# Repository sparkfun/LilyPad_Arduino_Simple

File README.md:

LilyPad Arduino Simple
======================

[*LilyPad Arduino Simple Board (DEV-10274)*](https://www.sparkfun.com/products/10274)

This LilyPad board is smaller than the LilyPad Main Board, with fewer pins. However, it does have a 
built-in power supply socket, and an on/off switch. 

Repository Contents
-------------------

* **/Hardware** - All Eagle design files (.brd, .sch, .STL)
* **/Production** - Test bed files and production panel files

License Information
-------------------
The hardware is released under [Creative Commons ShareAlike 4.0 International](https://creativecommons.org/licenses/by-sa/4.0/).
The code is beerware; if you see me (or any other SparkFun employee) at the local, and you've found our code helpful, please buy us a round!

Distributed as-is; no warranty is given.

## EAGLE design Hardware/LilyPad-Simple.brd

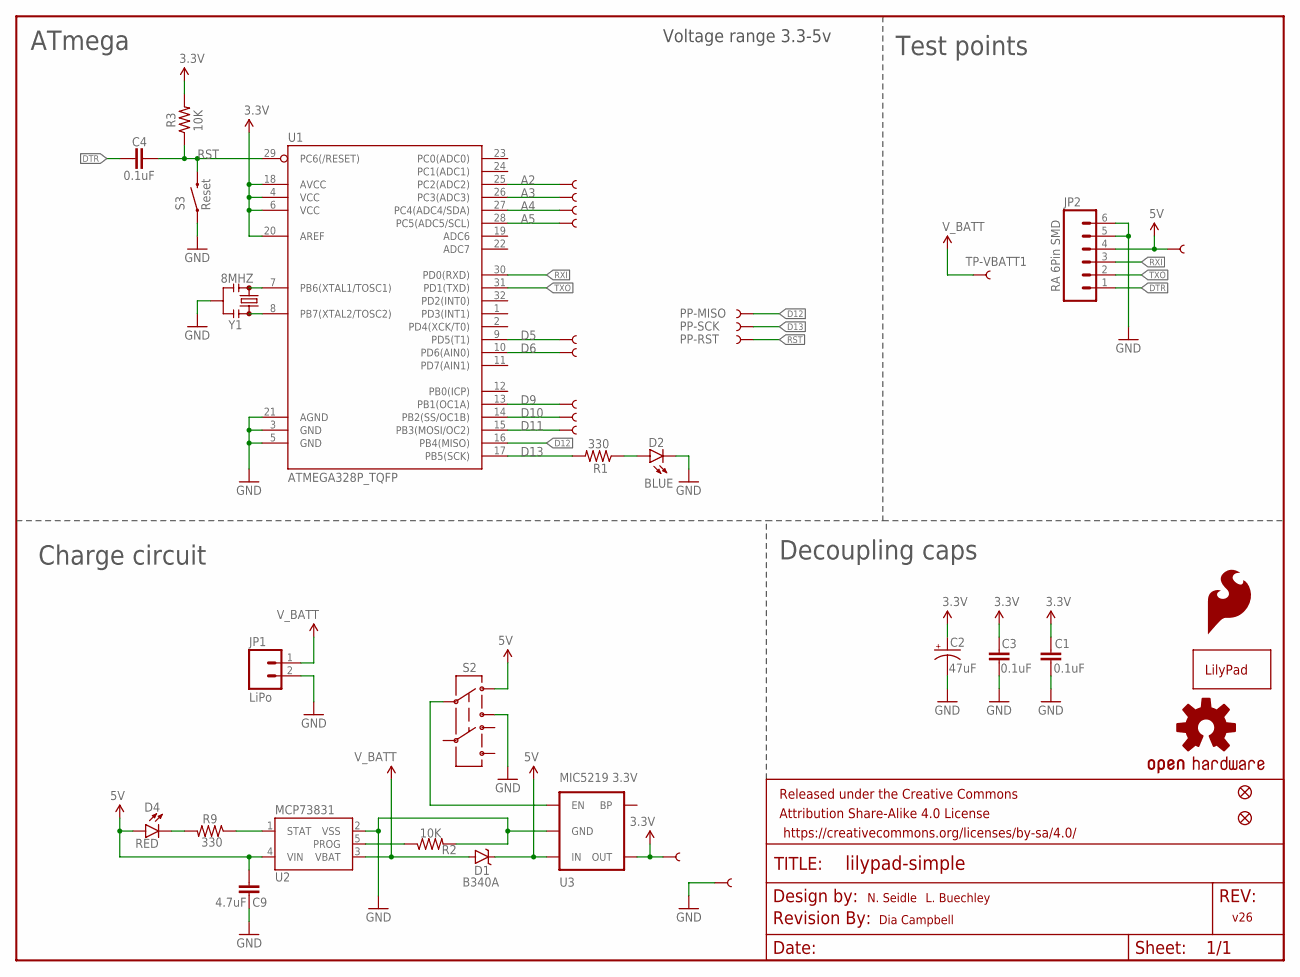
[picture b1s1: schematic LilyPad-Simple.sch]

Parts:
A2/16, A3/17, A4/18, A5/19: SEWTAP9; PETAL-LONG-1-2SIDE
C1, C3, C4: 0.1uF; 0603-CAP
C2: 47uF; EIA3528
C9: 4.7uF; 0603-CAP
D1: B340A; SMA-DIODE
D2: BLUE; LED-0603
D4: RED; LED-0603
FID1, FID2: FIDUCIAL1X2; FIDUCIAL-1X2
FRAME1: FRAME-LETTER; CREATIVE_COMMONS
JP1: LiPo; JST-2-SMD
JP2: RA 6Pin SMD; 1X06-SMD
LOGO1: OSHW-LOGOM-COPPER; OSHW-LOGO-M_COPPER
LOGO2: SFE_LOGO_FLAME.3COP; SFE_LOGO_FLAME_COPPER_.3
PP-MISO: TEST-POINT3X5; PAD.03X.05
PP-RST: TEST-POINT3X5; PAD.03X.05
PP-SCK: TEST-POINT3X5; PAD.03X.05
R1, R9: 330; 0603-RES
R2, R3: 10K; 0603-RES
S2: DPDT; AYZ0202
S3: Reset; TACTILE-SWITCH-SMD
TP-FTDI_VCC: TEST-POINT3X5; PAD.03X.05
TP-VBATT1: TEST-POINT3X5; PAD.03X.05
U1: ATMEGA328P_TQFP; TQFP32-08
U2: MCP73831; SOT23-5
U3: MIC5219 3.3V; SOT23-5
U$1: REVISION
U$2: LOGO-LPLPA; LOGO-LPA
U$4, U$35, U$37, U$39, U$41, U$43, U$45: SEWTAP9; PETAL-LONG-1-2SIDE
Y1: 8MHZ; RESONATOR-SMD

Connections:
3.3V: C1.1, C2.A (+), C3.1, R3.2, U1.4 (VCC), U1.6 (VCC), U1.18 (AVCC), U1.20 (AREF), U3.5 (OUT), U$45.1
5V: C9.1, D1.C, D4.A, JP2.4, S2.1, TP-FTDI_VCC.P$1, U2.4 (VIN), U3.1 (IN)
A2: A2/16.1, U1.25 (PC2(ADC2))
A3: A3/17.1, U1.26 (PC3(ADC3))
A4: A4/18.1, U1.27 (PC4(ADC4/SDA))
A5: A5/19.1, U1.28 (PC5(ADC5/SCL))
D5: U1.9 (PD5(T1)), U$41.1
D6: U1.10 (PD6(AIN0)), U$35.1
D9: U1.13 (PB1(OC1A)), U$37.1
D10: U1.14 (PB2(SS/OC1B)), U$39.1
D11: U1.15 (PB3(MOSI/OC2)), U$4.1
D12: PP-MISO.P$1, U1.16 (PB4(MISO))
D13: PP-SCK.P$1, R1.2, U1.17 (PB5(SCK))
DTR: C4.1, JP2.1
GND: C1.2, C2.C (-), C3.2, C9.2, D2.C, JP1.2 (1), JP2.5, JP2.6, R2.2, S2.3, S3.1, U1.3 (GND), U1.5 (GND), U1.21 (AGND), U2.2 (VSS), U3.2 (GND), U$43.1, Y1.2
unnamed: U1.7 (PB6(XTAL1/TOSC1)), Y1.1
unnamed: D2.A, R1.1
unnamed: U1.8 (PB7(XTAL2/TOSC2)), Y1.3
unnamed: R2.1, U2.5 (PROG)
unnamed: S2.2, U3.3 (EN)
unnamed: D4.C, R9.2
RST: C4.2, PP-RST.P$1, R3.1, S3.3 (2), U1.29 (PC6(/RESET))
RXI: JP2.3, U1.30 (PD0(RXD))
STAT: R9.1, U2.1 (STAT)
TXO: JP2.2, U1.31 (PD1(TXD))
V_BATT: D1.A, JP1.1 (2), TP-VBATT1.P$1, U2.3 (VBAT)

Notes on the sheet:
L. Buechley
N. Seidle
Dia Campbell
v26
Charge circuit
Decoupling caps
Test points
ATmega
Voltage range 3.3-5v

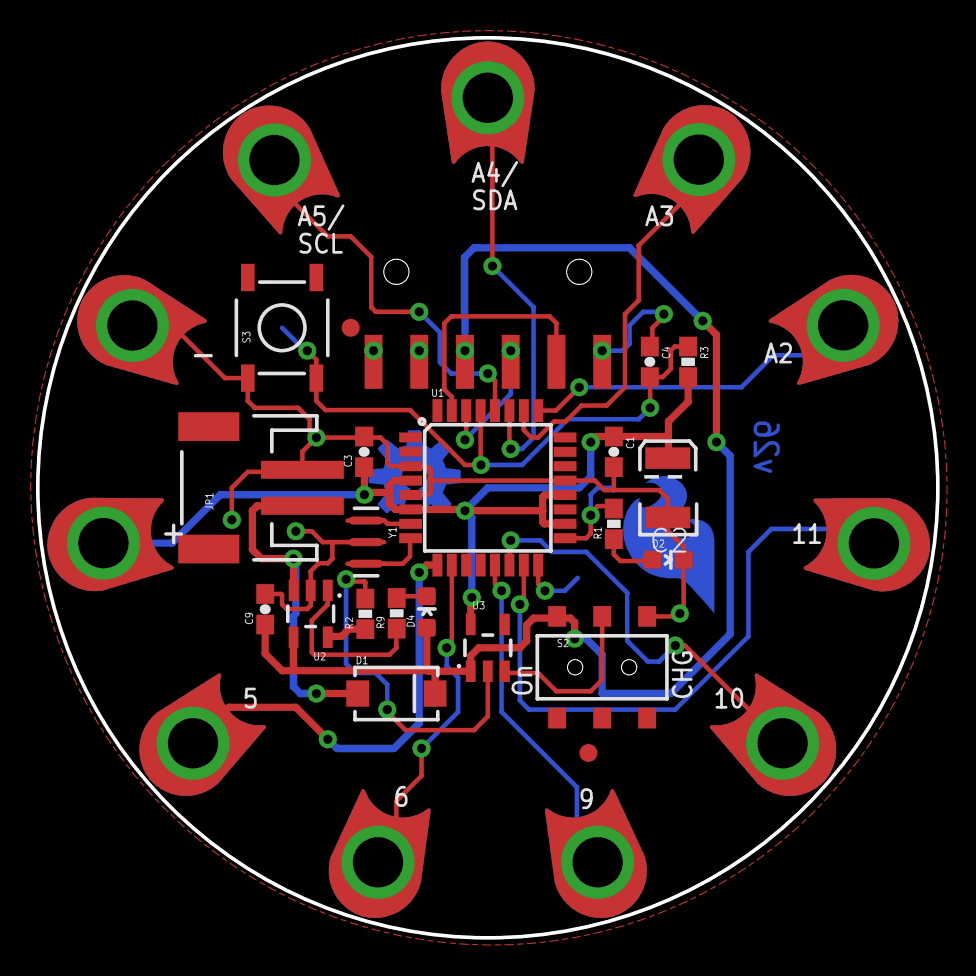
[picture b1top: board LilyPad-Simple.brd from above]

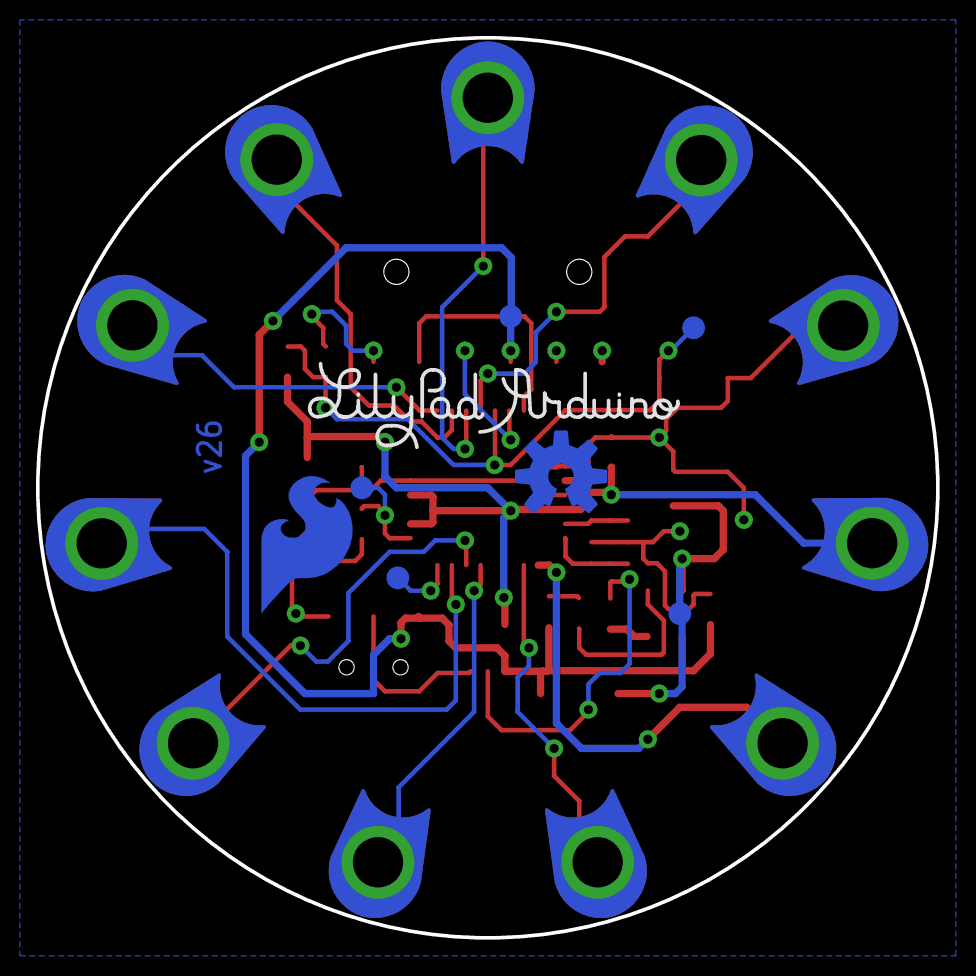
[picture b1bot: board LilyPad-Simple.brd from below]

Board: 2 copper layers, 50.0 x 50.0 mm, 43 parts (8 on the bottom side), 26 nets.

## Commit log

2014-02-04 Initial file upload
2014-05-20 Updating README
2015-06-15 Revised to update footprints and improve charge circuit
2015-06-15 Remove v25 files
2015-06-15 Put test pads on grid, increased trace size on power supply pad
2015-06-19 DRC changes, fixed some errors
2015-07-29 Change to 3.3v connections
2015-07-30 fixed 3.3 routing
2015-08-11 Checklist edits
    Silk edited, TX and RX reconnected
2015-10-14 Adding ground pours for new aesthetic standards

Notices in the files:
parts and their libraries:
SparkFun-Aesthetics: Licensing: Creative Commons ShareAlike 4.0 International - https://creativecommons.org/licenses/by-sa/4.0
SparkFun-Aesthetics: Released under the Creative Commons Attribution Share-Alike 4.0 License
SparkFun-Aesthetics: Released under the Creative Commons
